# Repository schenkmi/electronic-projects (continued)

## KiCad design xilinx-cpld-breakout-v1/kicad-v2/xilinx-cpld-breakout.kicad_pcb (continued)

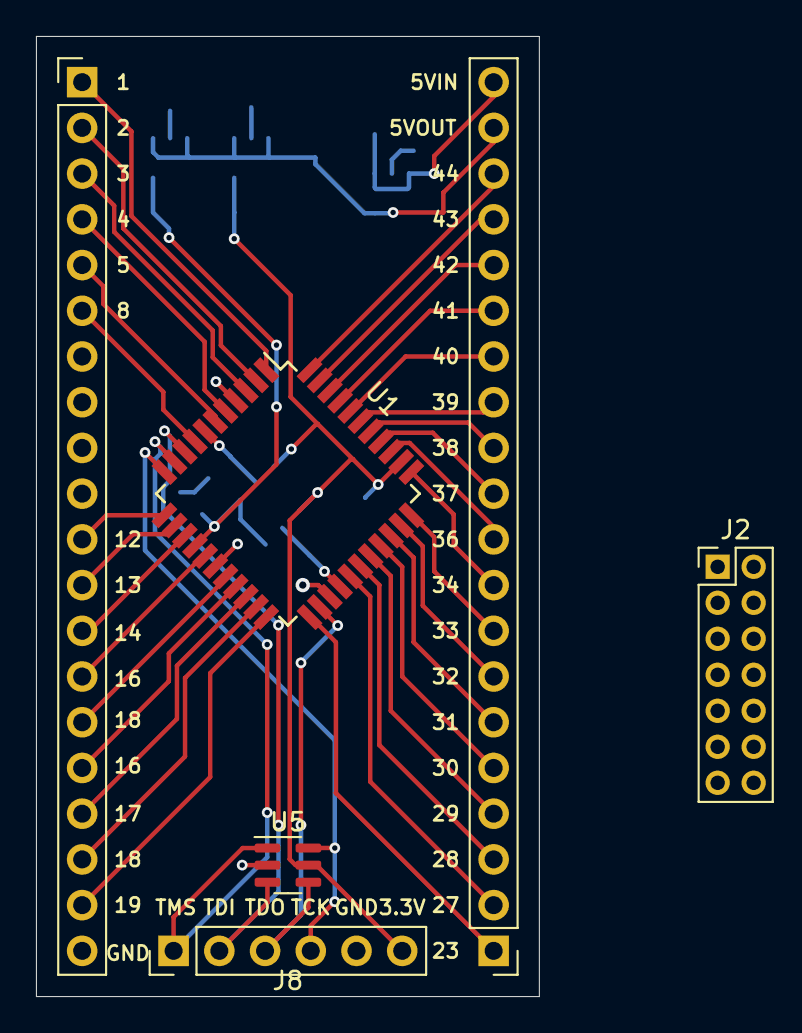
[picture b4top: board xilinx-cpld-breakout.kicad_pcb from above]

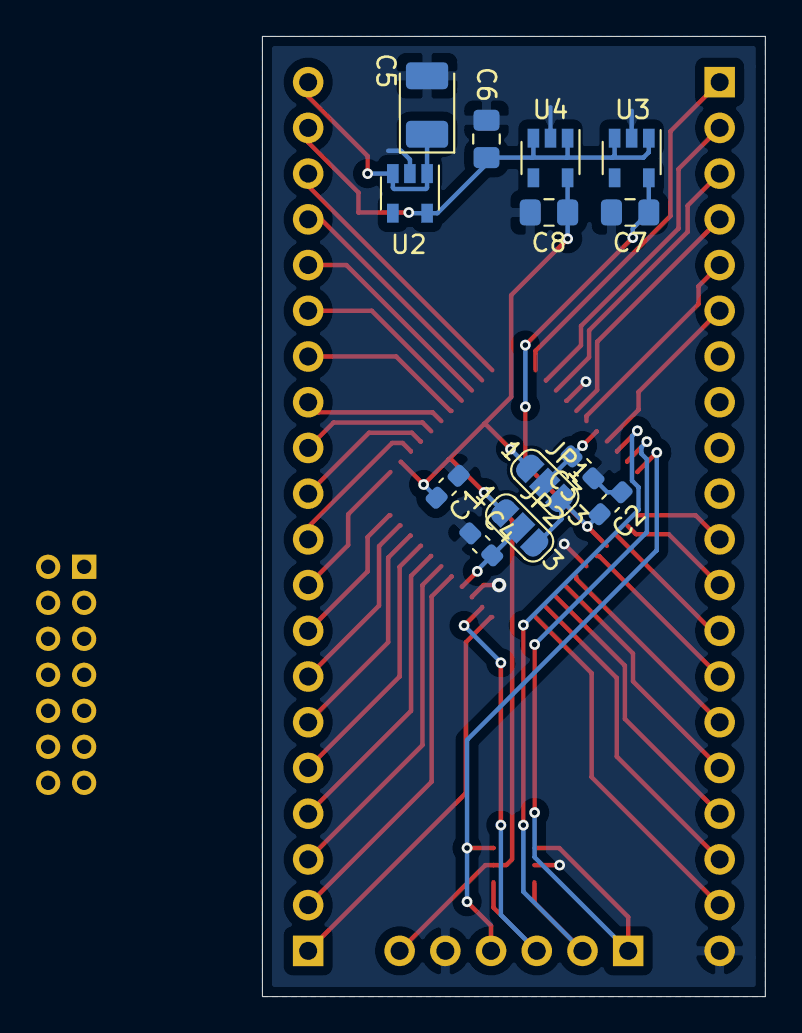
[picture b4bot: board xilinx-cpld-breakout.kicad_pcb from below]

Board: 2 copper layers, 27.9 x 53.3 mm, 19 parts (13 on the bottom side), 44 nets.
